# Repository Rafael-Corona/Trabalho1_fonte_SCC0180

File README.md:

# Trabalho1_fonte_SCC0180
Trabalho 1 da disciplina Eletrônica para computação, uma fonte de tensão 3v~12v, 100mA.

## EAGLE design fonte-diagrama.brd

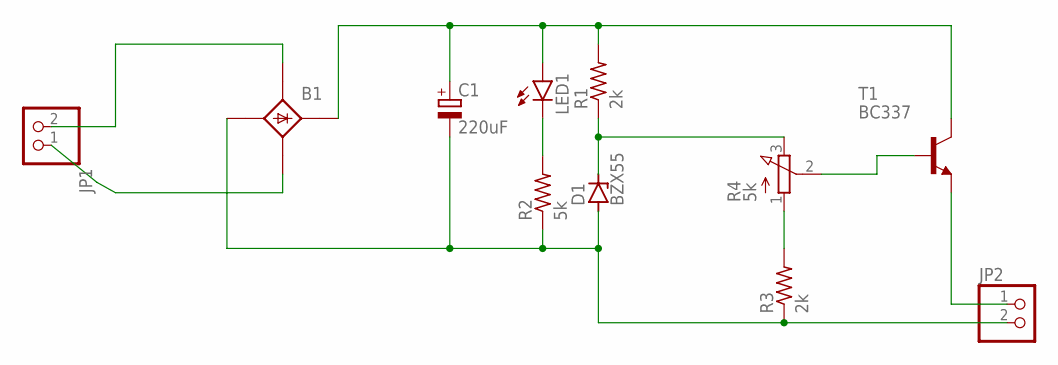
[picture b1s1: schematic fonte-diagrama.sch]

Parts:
B1: B25A-
C1: 220uF; EB20D
D1: BZX55; DO35Z10
JP1, JP2: PINHD-1X2; 1X02
LED1: LED5MM
R1, R3: 2k; 0207/10
R2: 5k; 0207/10
R4: 5k; 3RP/1610N
T1: BC337; TO92

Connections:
unnamed: B1.AC1- (AC1), JP1.2
unnamed: B1.AC2- (AC2), JP1.1
unnamed: B1.+1 (+), C1.+, LED1.A, R1.2, T1.3 (C)
unnamed: B1.-1 (-), C1.-, D1.A, JP2.2, R2.1, R3.1
unnamed: LED1.K (C), R2.2
unnamed: D1.C, R1.1, R4.3 (E)
unnamed: R3.2, R4.1 (A)
unnamed: R4.2 (S), T1.2 (B)
unnamed: JP2.1, T1.1 (E)

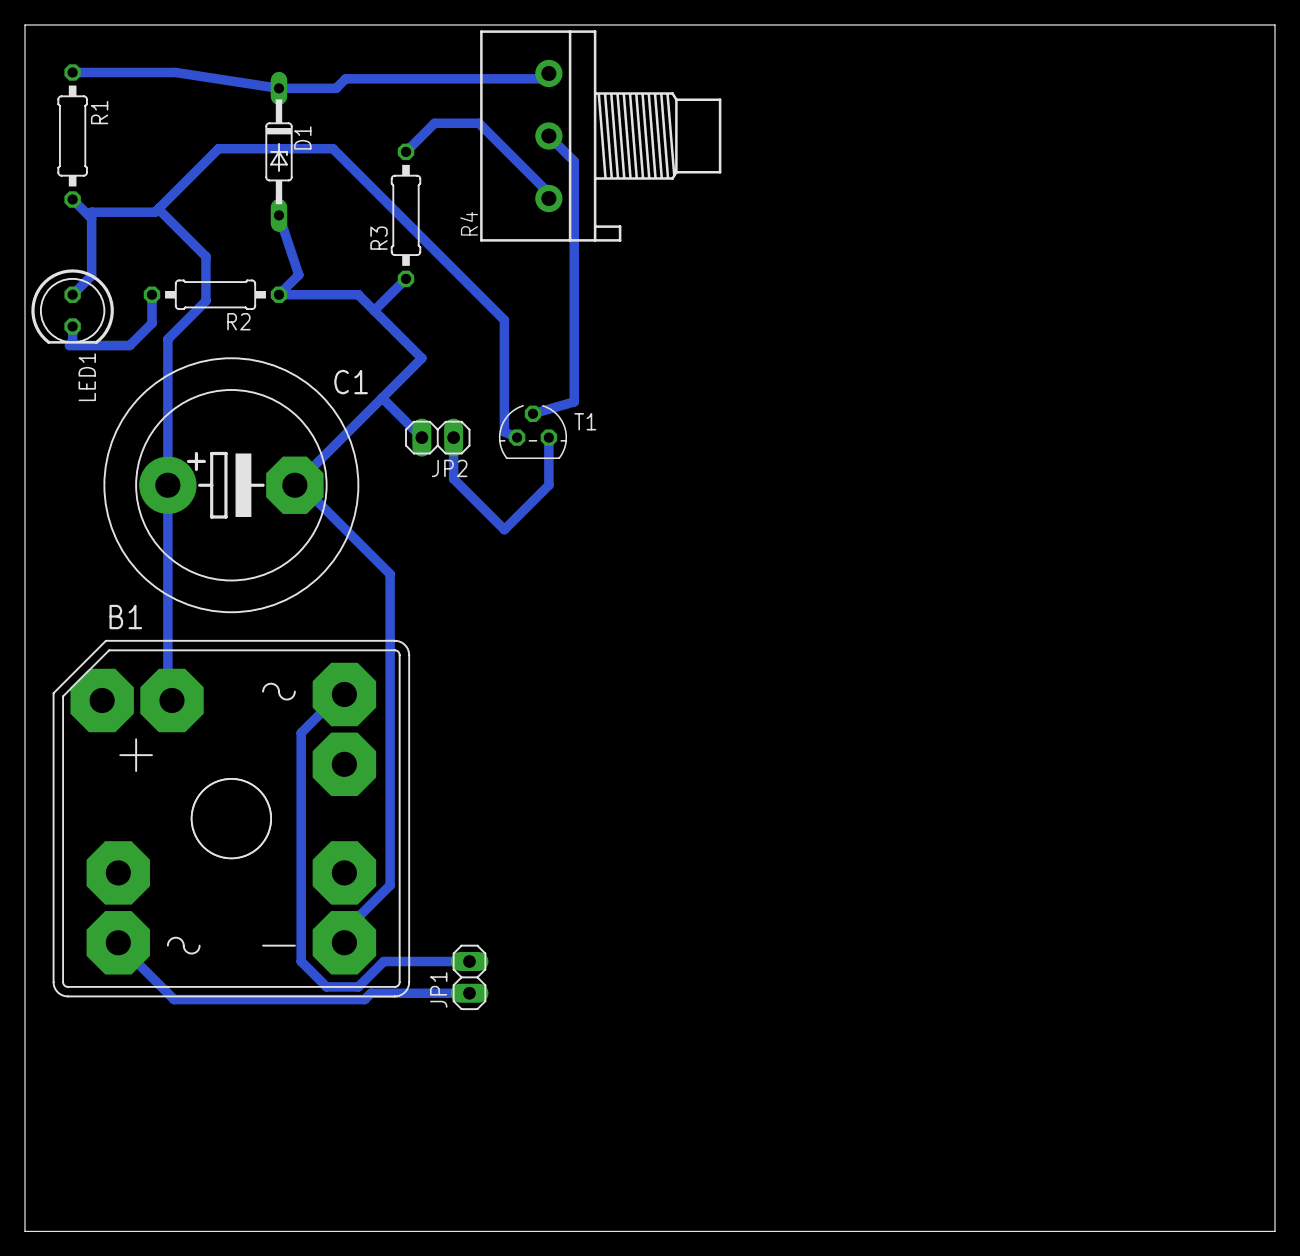
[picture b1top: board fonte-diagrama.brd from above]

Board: 2 copper layers, 100.0 x 96.5 mm, 11 parts (0 on the bottom side), 9 nets.

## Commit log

2020-07-01 Create Lista de componentes
2020-07-01 Update Lista de componentes
2020-07-02 Create Simulação
2020-07-08 Diagrama do circuito no EAGLE
2020-07-14 Create Vídeo
